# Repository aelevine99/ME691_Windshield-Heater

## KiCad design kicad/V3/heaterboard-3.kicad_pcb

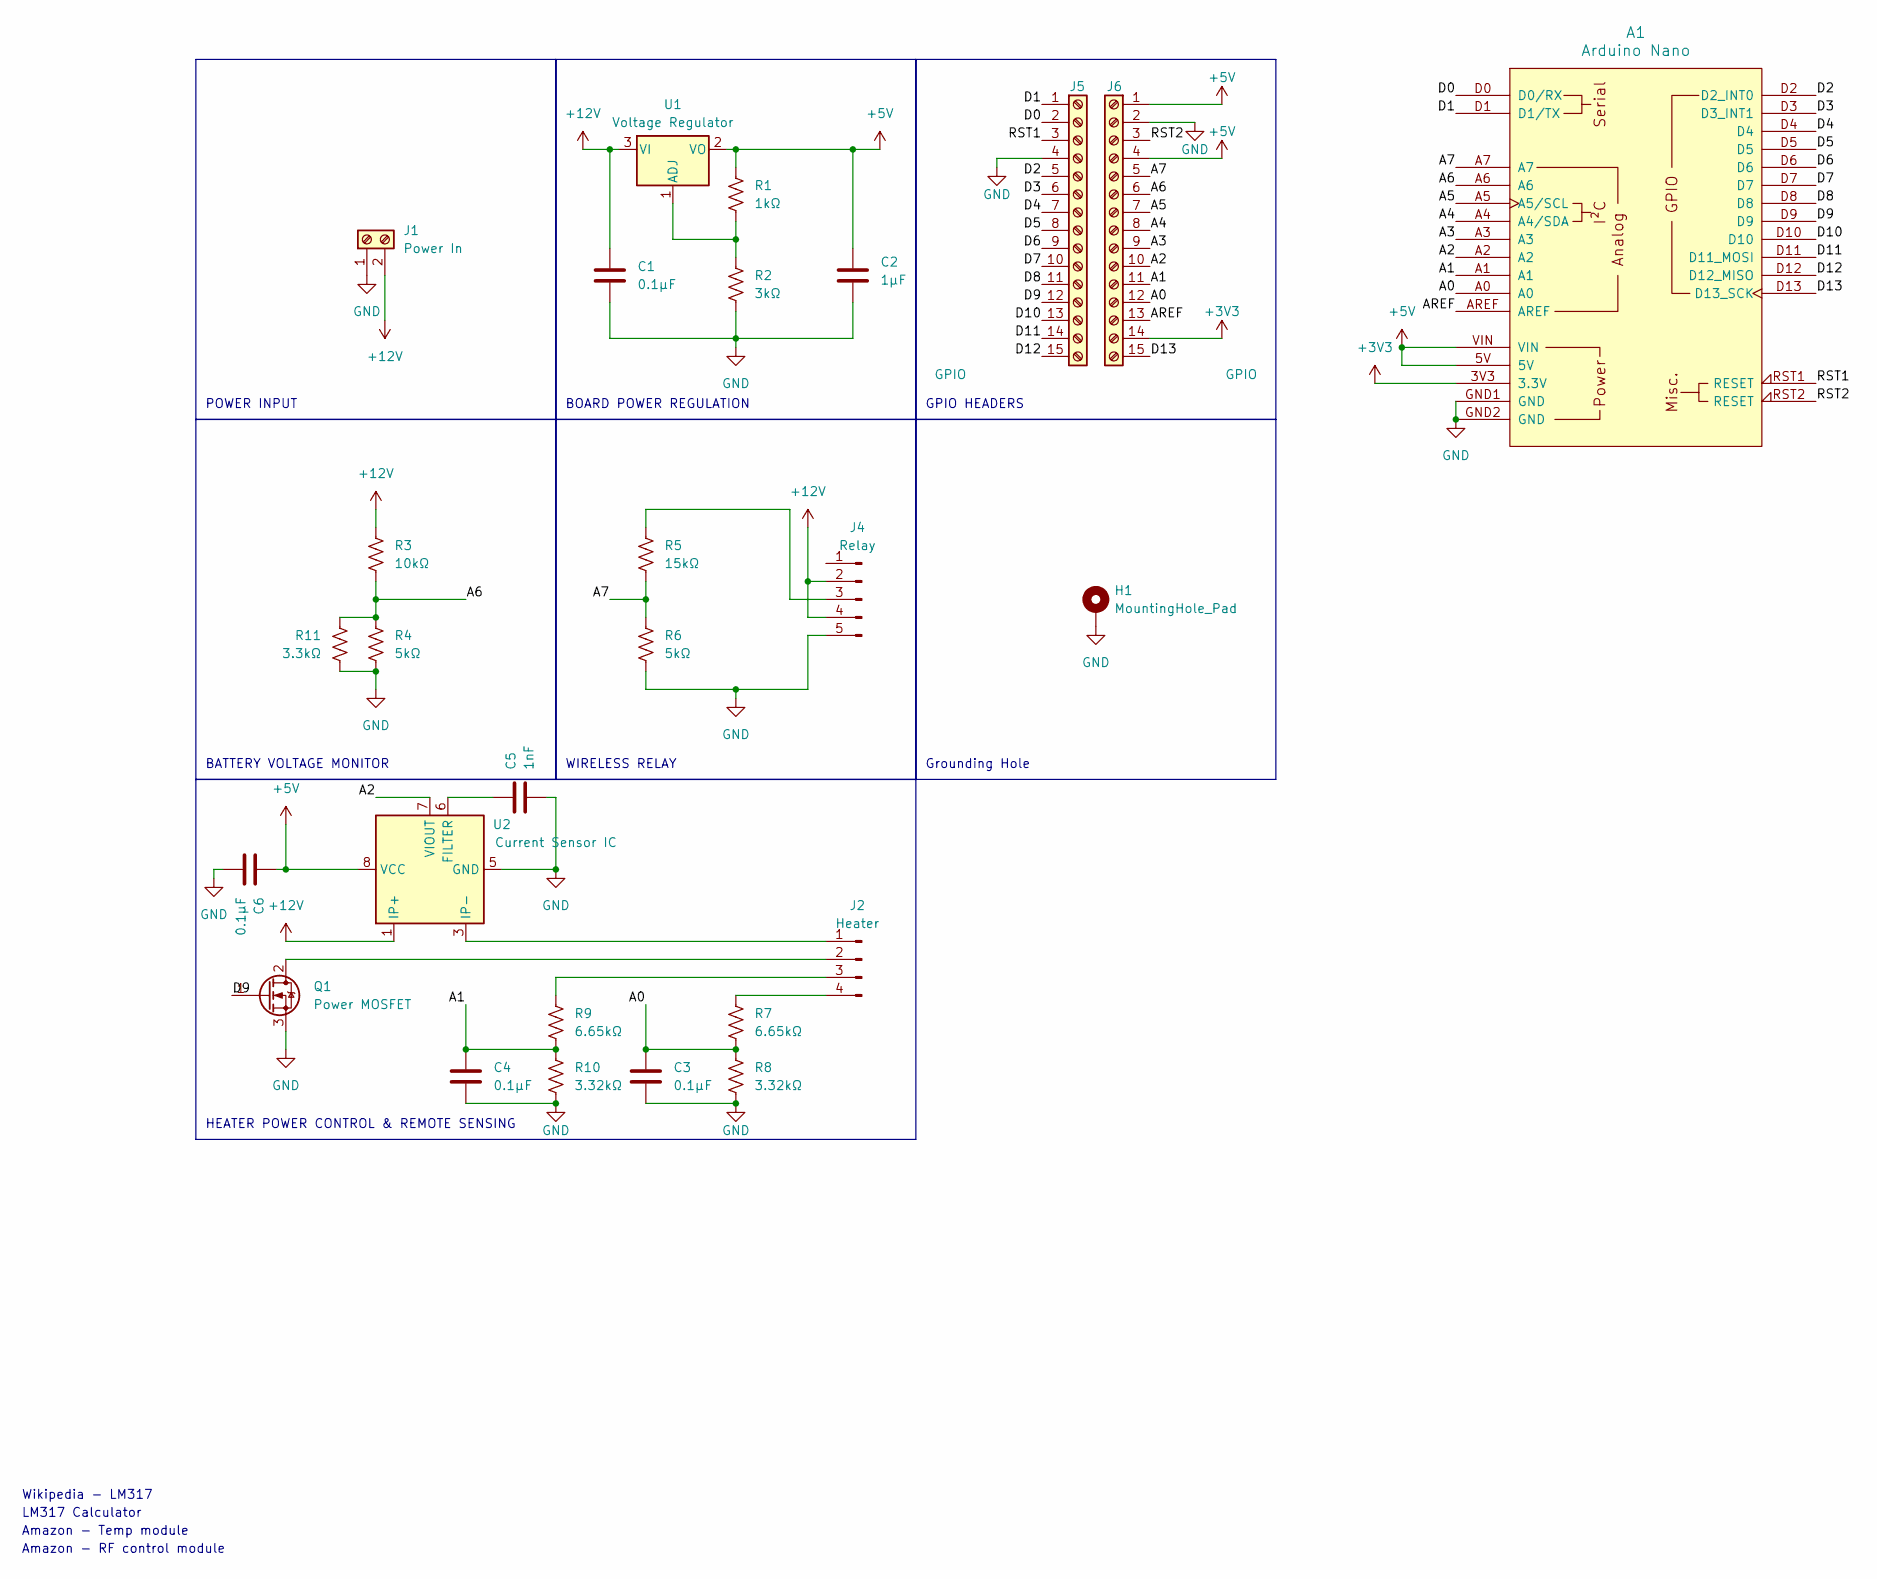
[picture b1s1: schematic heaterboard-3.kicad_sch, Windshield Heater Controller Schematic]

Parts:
A1: Arduino Nano; Arduino_Nano_Socket
C1, C3, C4, C6: 0.1μF; C_1206_3216Metric_Pad1.33x1.80mm_HandSolder
C2: 1μF; C_1206_3216Metric_Pad1.33x1.80mm_HandSolder
C5: 1nF; C_1206_3216Metric_Pad1.33x1.80mm_HandSolder
H1: MountingHole_Pad; MountingHole_3.2mm_M3_Pad
J1: Power In; Molex_Mega-Fit_76825-0002_2x01_P5.70mm_Horizontal
J2: Heater; Molex_Mega-Fit_76825-0004_2x02_P5.70mm_Horizontal
J4: Relay; Molex_Micro-Fit_3.0_43650-0515_1x05_P3.00mm_Vertical
J5, J6: GPIO; PinSocket_1x15_P2.54mm_Vertical
Q1: Power MOSFET; TO-220-3_Vertical
R1: 1kΩ; R_1206_3216Metric_Pad1.30x1.75mm_HandSolder
R2: 3kΩ; R_1206_3216Metric_Pad1.30x1.75mm_HandSolder
R3: 10kΩ; R_1206_3216Metric_Pad1.30x1.75mm_HandSolder
R4, R6: 5kΩ; R_1206_3216Metric_Pad1.30x1.75mm_HandSolder
R5: 15kΩ; R_1206_3216Metric_Pad1.30x1.75mm_HandSolder
R7, R9: 6.65kΩ; R_1206_3216Metric_Pad1.30x1.75mm_HandSolder
R8, R10: 3.32kΩ; R_1206_3216Metric_Pad1.30x1.75mm_HandSolder
R11: 3.3kΩ
U1: Voltage Regulator; TO-220-3_Vertical
U2: Current Sensor IC; SOIC-8_3.9x4.9mm_P1.27mm

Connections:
+3V3: A1.3V3 (3.3V), J6.14
+5V: A1.5V, A1.VIN, C2.1, C6.1, J6.1, J6.4, R1.1, U1.2 (VO), U2.8 (VCC)
+12V: C1.1, J1.2, J4.2, J4.4, R3.1, U1.3 (VI), U2.1 (IP+), U2.2 (IP+)
/A0: A1.A0, C3.1, J6.12, R7.2, R8.1
/A1: A1.A1, C4.1, J6.11, R9.2, R10.1
/A2: A1.A2, J6.10, U2.7 (VIOUT)
/A3: A1.A3, J6.9
/A4: A1.A4 (A4/SDA), J6.8
/A5: A1.A5 (A5/SCL), J6.7
/A6: A1.A6, J6.6, R3.2, R4.1, R11.1
/A7: A1.A7, J6.5, R5.2, R6.1
/AREF: A1.AREF, J6.13
/D0: A1.D0 (D0/RX), J5.2
/D1: A1.D1 (D1/TX), J5.1
/D2: A1.D2 (D2_INT0), J5.5
/D3: A1.D3 (D3_INT1), J5.6
/D4: A1.D4, J5.7
/D5: A1.D5, J5.8
/D6: A1.D6, J5.9
/D7: A1.D7, J5.10
/D8: A1.D8, J5.11
/D9: A1.D9, J5.12, Q1.1 (G)
/D10: A1.D10, J5.13
/D11: A1.D11 (D11_MOSI), J5.14
/D12: A1.D12 (D12_MISO), J5.15
/D13: A1.D13 (D13_SCK), J6.15
/RST1: A1.RST1 (RESET), J5.3
/RST2: A1.RST2 (RESET), J6.3
GND: A1.GND1 (GND), A1.GND2 (GND), C1.2, C2.2, C3.2, C4.2, C5.2, C6.2, H1.1, J1.1, J4.5, J5.4, J6.2, Q1.3 (S), R2.2, R4.2, R6.2, R8.2, R10.2, R11.2, U2.5 (GND)
unnamed: J2.1, U2.3 (IP-), U2.4 (IP-)
unnamed: J2.2, Q1.2 (D)
unnamed: J2.3, R9.1
unnamed: J2.4, R7.1
unnamed: J4.3, R5.1
unnamed: R1.2, R2.1, U1.1 (ADJ)
unnamed: C5.1, U2.6 (FILTER)

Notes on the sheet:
Wikipedia - LM317
BATTERY VOLTAGE MONITOR
BOARD POWER REGULATION
POWER INPUT
Amazon - RF control module
Grounding Hole
HEATER POWER CONTROL & REMOTE SENSING
Amazon - Temp module
WIRELESS RELAY
LM317 Calculator
GPIO HEADERS

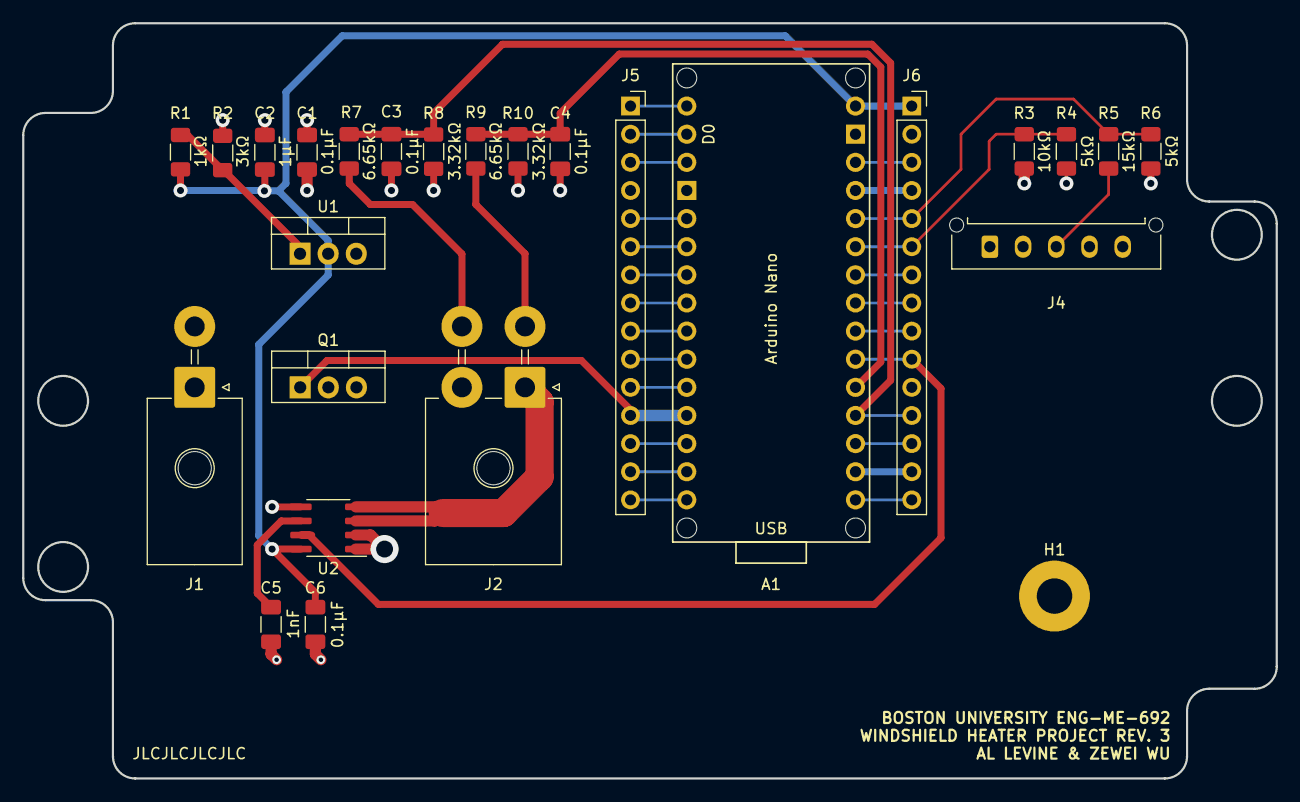
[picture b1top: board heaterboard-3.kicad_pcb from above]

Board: 4 copper layers, 113.2 x 68.2 mm, 26 parts (0 on the bottom side), 36 nets.

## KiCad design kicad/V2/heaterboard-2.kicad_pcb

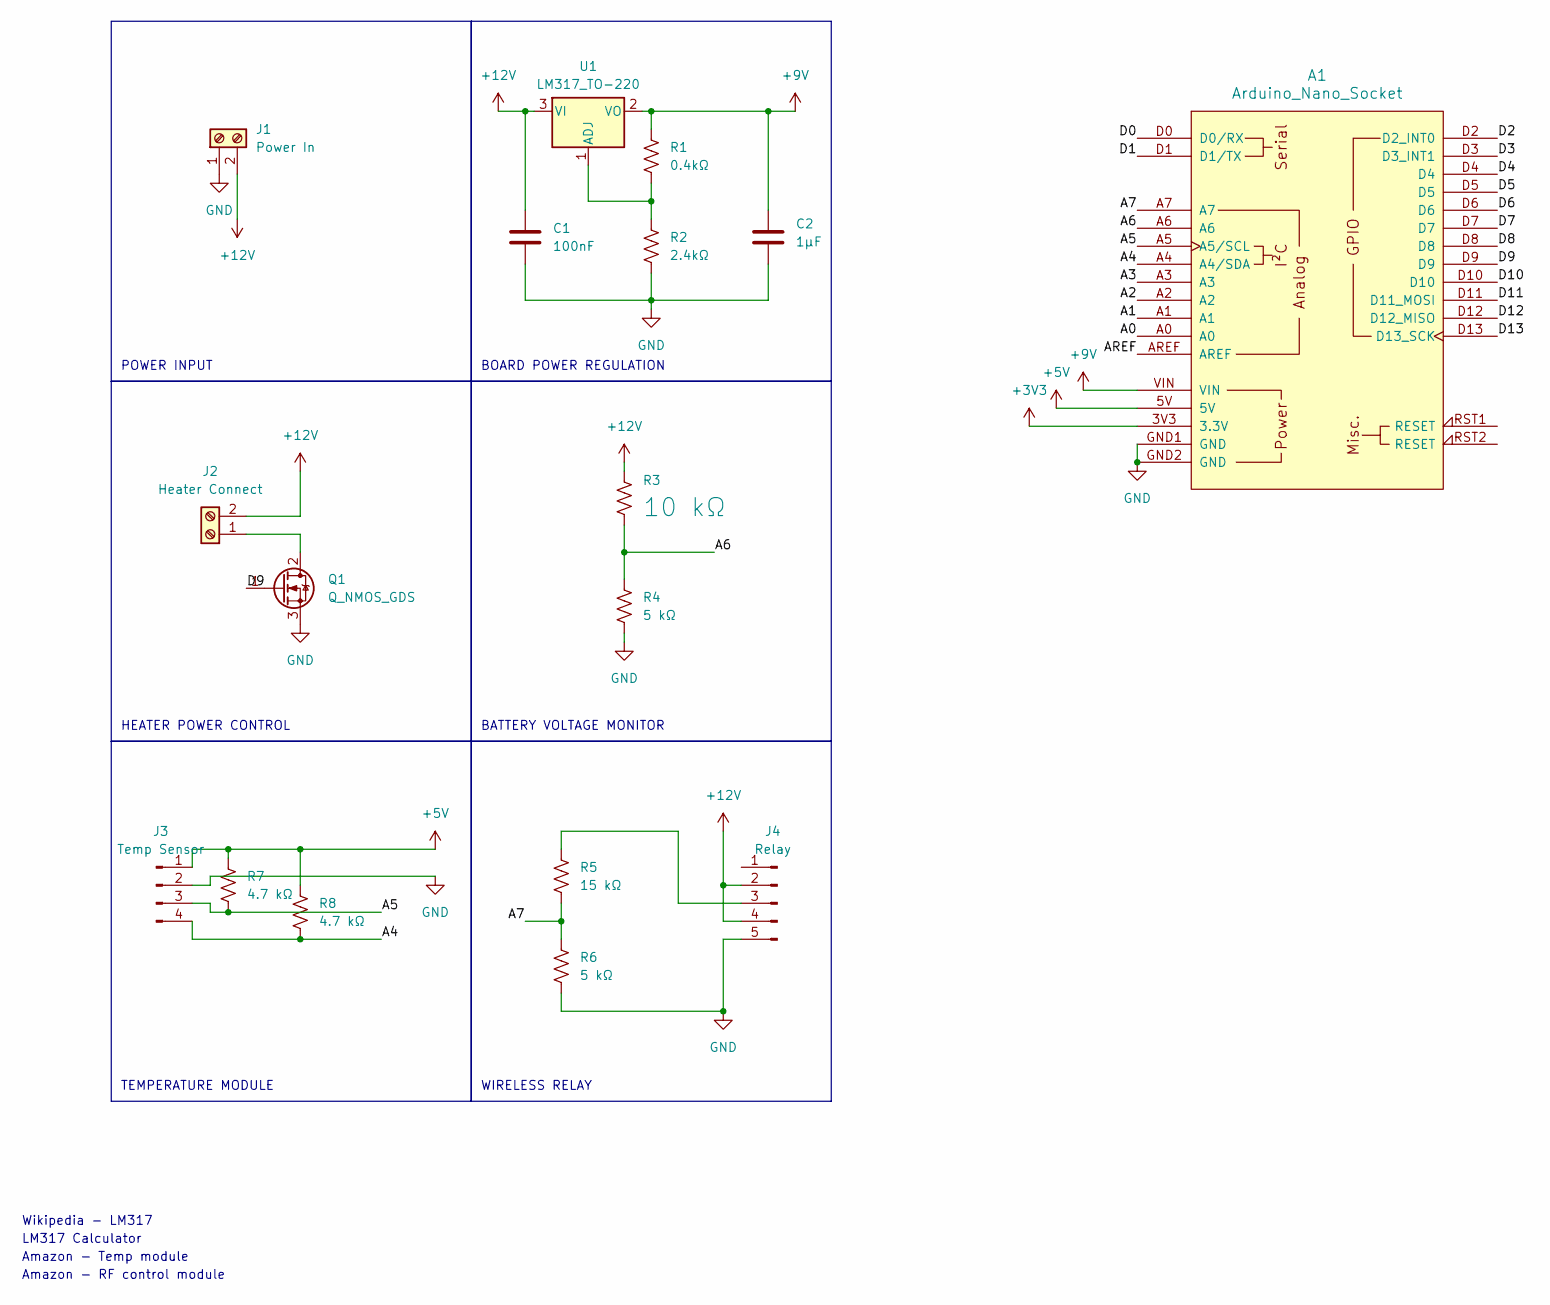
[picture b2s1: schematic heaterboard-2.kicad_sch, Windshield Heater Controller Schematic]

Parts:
A1: Arduino_Nano_Socket
C1: 100nF; C_1206_3216Metric_Pad1.33x1.80mm_HandSolder
C2: 1μF; C_1206_3216Metric_Pad1.33x1.80mm_HandSolder
J1: Power In; Molex_Mega-Fit_76825-0002_2x01_P5.70mm_Horizontal
J2: Heater Connect; Molex_Mega-Fit_76825-0002_2x01_P5.70mm_Horizontal
J3: Temp Sensor; Molex_Micro-Fit_3.0_43650-0400_1x04_P3.00mm_Horizontal
J4: Relay; Molex_Micro-Fit_3.0_43650-0515_1x05_P3.00mm_Vertical
Q1: Q_NMOS_GDS; TO-220-3_Vertical
R1: 0.4kΩ; R_1206_3216Metric_Pad1.30x1.75mm_HandSolder
R2: 2.4kΩ; R_1206_3216Metric_Pad1.30x1.75mm_HandSolder
R3: 10 kΩ; R_1206_3216Metric_Pad1.30x1.75mm_HandSolder
R4, R6: 5 kΩ; R_1206_3216Metric_Pad1.30x1.75mm_HandSolder
R5: 15 kΩ; R_1206_3216Metric_Pad1.30x1.75mm_HandSolder
R7, R8: 4.7 kΩ; R_1206_3216Metric_Pad1.30x1.75mm_HandSolder
U1: LM317_TO-220; TO-220-3_Vertical

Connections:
+3V3: A1.3V3 (3.3V)
+5V: A1.5V, J3.1, R7.1, R8.1
+9V: A1.VIN, C2.1, R1.1, U1.2 (VO)
+12V: C1.1, J1.2, J2.2, J4.2, J4.4, R3.1, U1.3 (VI)
/A0: A1.A0
/A1: A1.A1
/A2: A1.A2
/A3: A1.A3
/A4: A1.A4 (A4/SDA), J3.4, R8.2
/A5: A1.A5 (A5/SCL), J3.3, R7.2
/A6: A1.A6, R3.2, R4.1
/A7: A1.A7, R5.2, R6.1
/AREF: A1.AREF
/D0: A1.D0 (D0/RX)
/D1: A1.D1 (D1/TX)
/D2: A1.D2 (D2_INT0)
/D3: A1.D3 (D3_INT1)
/D4: A1.D4
/D5: A1.D5
/D6: A1.D6
/D7: A1.D7
/D8: A1.D8
/D9: A1.D9, Q1.1 (G)
/D10: A1.D10
/D11: A1.D11 (D11_MOSI)
/D12: A1.D12 (D12_MISO)
/D13: A1.D13 (D13_SCK)
GND: A1.GND1 (GND), A1.GND2 (GND), C1.2, C2.2, J1.1, J3.2, J4.5, Q1.3 (S), R2.2, R4.2, R6.2
unnamed: J2.1, Q1.2 (D)
unnamed: J4.3, R5.1
unnamed: R1.2, R2.1, U1.1 (ADJ)

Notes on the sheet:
Wikipedia - LM317
BATTERY VOLTAGE MONITOR
BOARD POWER REGULATION
POWER INPUT
Amazon - RF control module
HEATER POWER CONTROL
TEMPERATURE MODULE
Amazon - Temp module
WIRELESS RELAY
LM317 Calculator

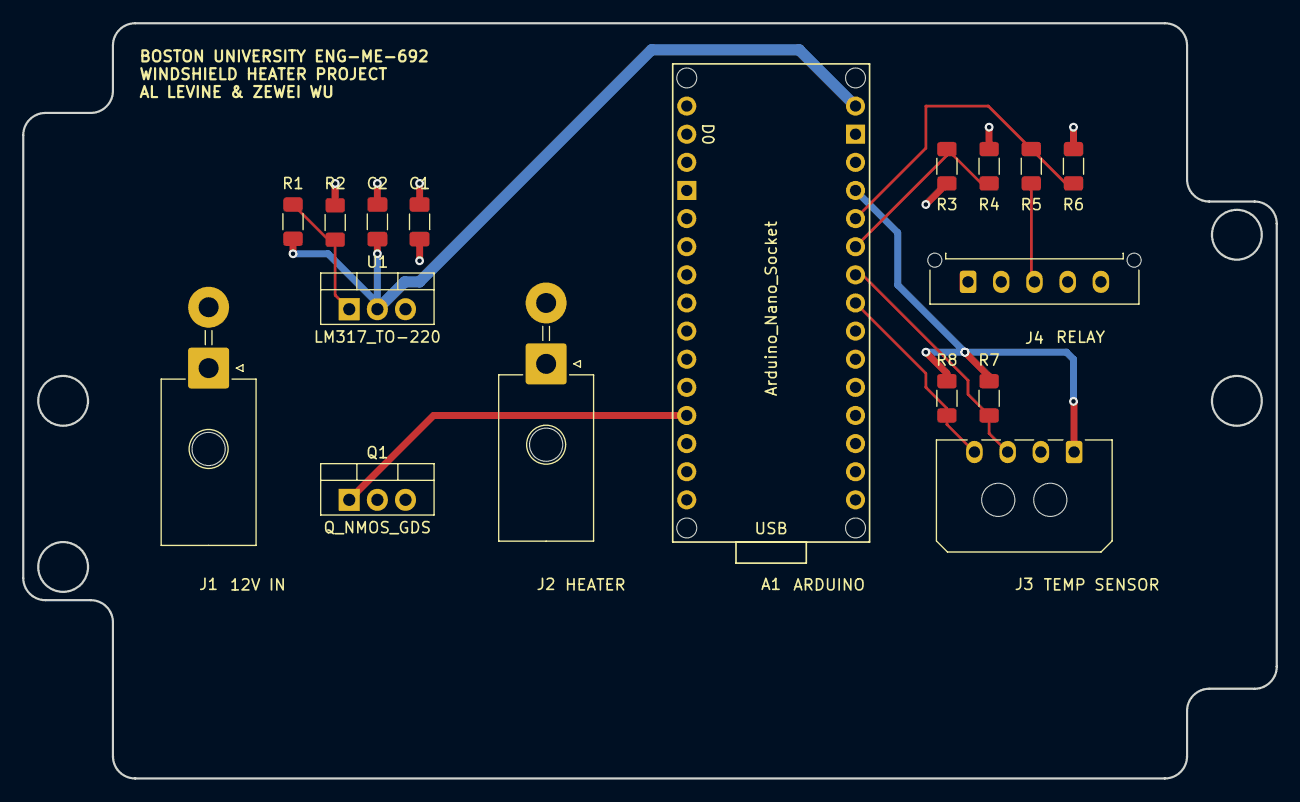
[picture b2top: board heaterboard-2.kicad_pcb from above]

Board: 4 copper layers, 113.2 x 68.2 mm, 17 parts (0 on the bottom side), 12 nets.

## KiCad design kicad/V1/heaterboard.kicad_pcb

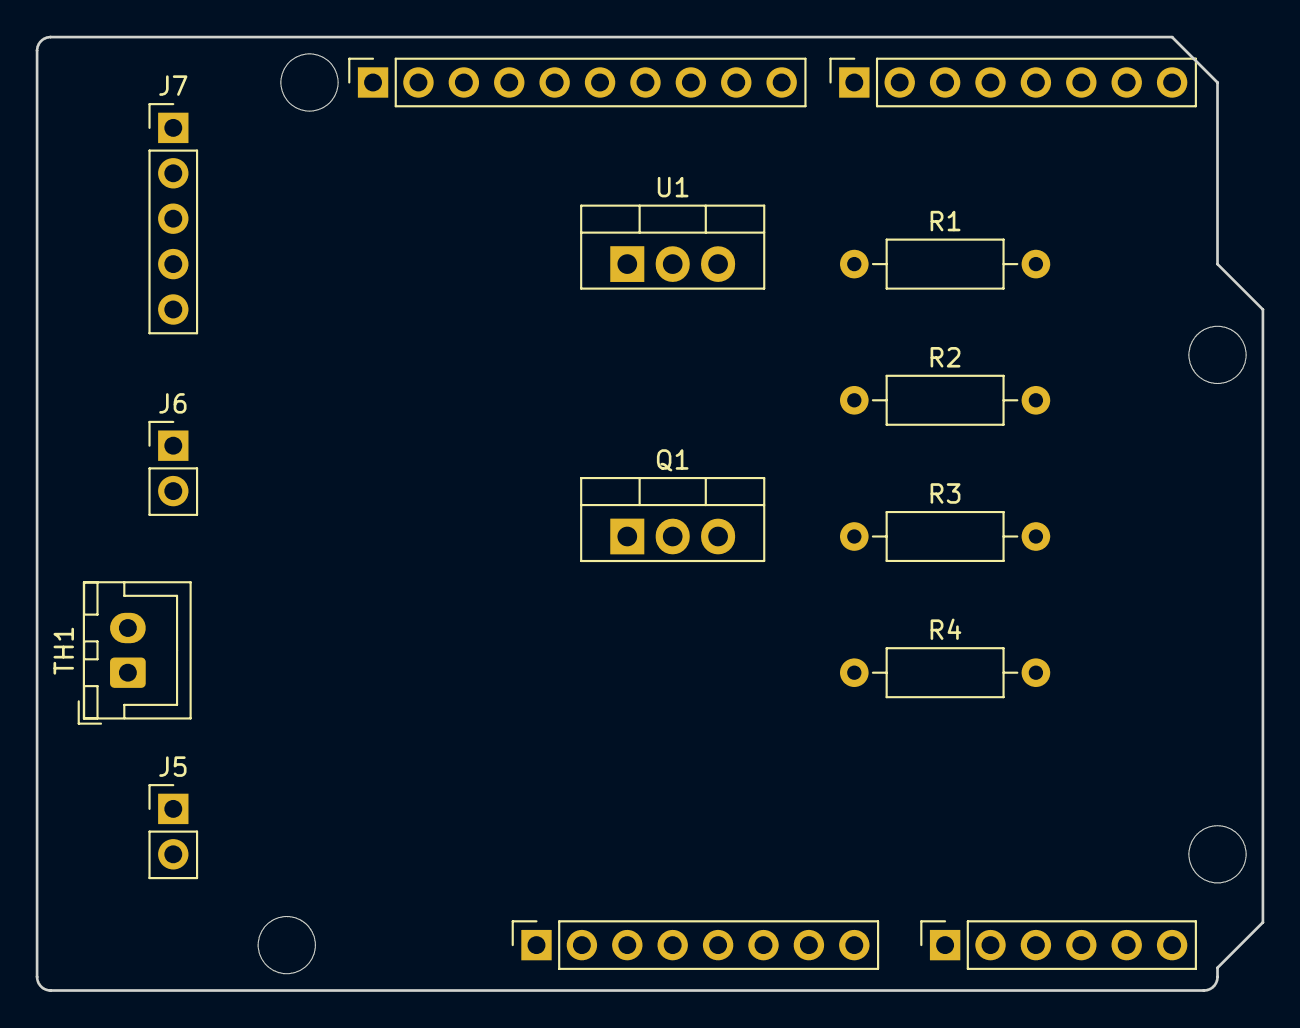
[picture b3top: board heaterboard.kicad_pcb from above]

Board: 4 copper layers, 68.6 x 53.3 mm, 18 parts (0 on the bottom side), 11 nets, no tracks yet.

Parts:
J1: Power; PinSocket_1x08_P2.54mm_Vertical
J2: Digital/PWM; PinSocket_1x10_P2.54mm_Vertical
J3: Analog; PinSocket_1x06_P2.54mm_Vertical
J4: Digital/PWM; PinSocket_1x08_P2.54mm_Vertical
J5, J6: Screw_Terminal_01x02; PinHeader_1x02_P2.54mm_Vertical
J7: Conn_01x05_Pin; PinHeader_1x05_P2.54mm_Vertical
MH1, MH2, MH3, MH4: MountingHole_3.2mm
Q1: Q_NMOS_GDS; TO-220-3_Vertical
R1: 10 kΩ; R_Axial_DIN0207_L6.3mm_D2.5mm_P10.16mm_Horizontal
R2, R4: 5 kΩ; R_Axial_DIN0207_L6.3mm_D2.5mm_P10.16mm_Horizontal
R3: 15 kΩ; R_Axial_DIN0207_L6.3mm_D2.5mm_P10.16mm_Horizontal
TH1: PT100; JST_XH_B2B-XH-A_1x02_P2.50mm_Vertical
U1: LM7805_TO220; TO-220-3_Vertical

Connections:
/*3: J4.5, Q1.1 (G)
/A1: J3.2, R3.2 (-), R4.1 (+)
/A2: J3.3, TH1.2
/A3: J3.4, R1.2 (-), R2.1 (+)
/SCL/A5: J2.1, J3.6
/SDA/A4: J2.2, J3.5
unnamed: J1.6, J1.7, U1.2 (GND)
unnamed: J6.1, Q1.2 (D)
unnamed: J7.2, J7.4
unnamed: J7.3, R3.1 (+)
unnamed: J7.5, R4.2 (-)

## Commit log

2024-01-23 project creation
2024-01-23 added mfg package
2024-01-23 end of class 23 jan
2024-01-25 end of class 25 jan
2024-01-30 design pass 1
2024-01-30 end of class 30 jan
2024-02-01 pivot to nano
2024-02-01 End of class 1 feb
2024-02-01 to-220
2024-02-06 02-06-2024
2024-02-06 added gitignore
2024-02-06 aeruigaeiurgaeur
2024-02-06 pcb stuff
2024-02-06 end of class 6 feb
2024-02-06 end class02-06-2024
2024-02-06 pcb updates
2024-02-08 pcb outline
2024-02-08 pcb layout
2024-02-13 pcb layout and began routing
2024-02-15 updated layout
2024-02-15 end of class 15 feb
2024-02-15 anothe end of class update
2024-02-15 more update
2024-02-15 Catalog No Update
    Catalog No Update
2024-02-15 Routing, parts, bom
2024-02-16 fixes
2024-02-16 gerbers
2024-02-16 gerbers fix
2024-02-16 added jlc order number location
2024-02-18 updated bom
2024-02-27 code
2024-03-05 code updates
2024-03-06 controller code
2024-03-06 more controller code updates
2024-03-07 created rev3
2024-03-22 board r3 update
2024-03-26 board r3 updates
2024-03-28 gerbers for pcb
2024-04-09 schematics printed
2024-04-30 code revision
2024-04-30 voltage divider, code updates
2024-05-01 code update
2024-05-02 final code update
2024-05-02 cad files
2024-05-06 photos
2024-05-06 Create LICENSE
